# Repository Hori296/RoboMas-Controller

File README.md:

# RoboMaster Controller

STM32を用いて設計・開発した、RoboMaster M2006 / M3508用モータコントローラです。

本リポジトリでは、回路設計・基板設計・ファームウェアを公開しています。
ロボット開発や組込みシステムで再利用できることを目的として製作しました。

---

## 概要

本コントローラは、DJI RoboMasterシリーズのM2006・M3508モータをCAN通信で制御するためのモータコントローラです。

速度制御・位置制御の両方に対応しており、連続角度推定やソフトウェアによる原点リセットなど、ロボット開発で扱いやすい機能を実装しています。

---

## 主な機能

- M2006 / M3508 モータ対応
- CAN通信による制御
- 速度制御（PID）
- 位置制御（カスケードPID）
- エンコーダ多回転角度推定
- ソフトウェア原点リセット
- 通信タイムアウト保護（500 ms）
- デバッグ情報送信（速度・位置誤差）
- RGB LEDによる状態表示

---

## 設計方針・意図

本コントローラは、M2006・M3508を今後のロボット開発で繰り返し利用できることを目的として設計しています。  
機能追加を前提とするのではなく、速度制御・位置制御・多回転角度推定・通信タイムアウト保護など、実際のロボット運用に必要な機能を一つの基板にまとめています。  
私自身がM2006・M3508モータを複数所有しており、今後のロボット開発でも継続して使用する予定です。そのため、毎回制御プログラムを作り直すことなく、共通で利用できるモータコントローラとして設計しました。

---

## ハードウェア

### マイコン

- STM32F446RE

### 通信

- CAN1
    - 上位PC・マイコンとの通信
- CAN2
    - RoboMaster ESCとの通信

### 制御周期

- 制御周期：1 ms（タイマ割り込み）
- CAN受信：受信割り込み

---

## 通信仕様

### 制御コマンド
|ID|num|
|---|---|
|0x221|motor1|
|0x222|motor2|
|0x223|motor3|
|0x224|motor4|

|Byte|内容|
|---|---|
|0|モータ種類|
|1|制御モード|
|2-3|目標値(int16 /1000)|
|4|Enable|
|5|角度リセット|
|6-7|予約|

### モータ種類

|値|内容|
|---|---|
|1|M2006|
|2|M3508|

### 制御モード

|値|内容|
|---|---|
|1|速度制御|
|2|位置制御|

### デバッグ情報

|ID|0~1|2~3|4~5|6~7|
|---|---|---|---|---|
|0x220|motor1_diff|motor2_diff|motor3_diff|motor4_diff|

---

## 安全機能

500 ms以上制御コマンドを受信しなかった場合、

- モータ停止
- PIDリセット
- 出力0

を実行し、通信断による暴走を防止します。

---

## 写真

|基板|3D|
|---|---|
|||

---

## 動作

※gif画像のためにいろいろしたら，LEDの色おかしくなった( ˊᵕˋ ;)

---

## フォルダ構成

```
Firmware/
    inc
    src
    README

PCB/
    pcb
    sch
    step
    production (JLCPCB発注用)
    README
```

---

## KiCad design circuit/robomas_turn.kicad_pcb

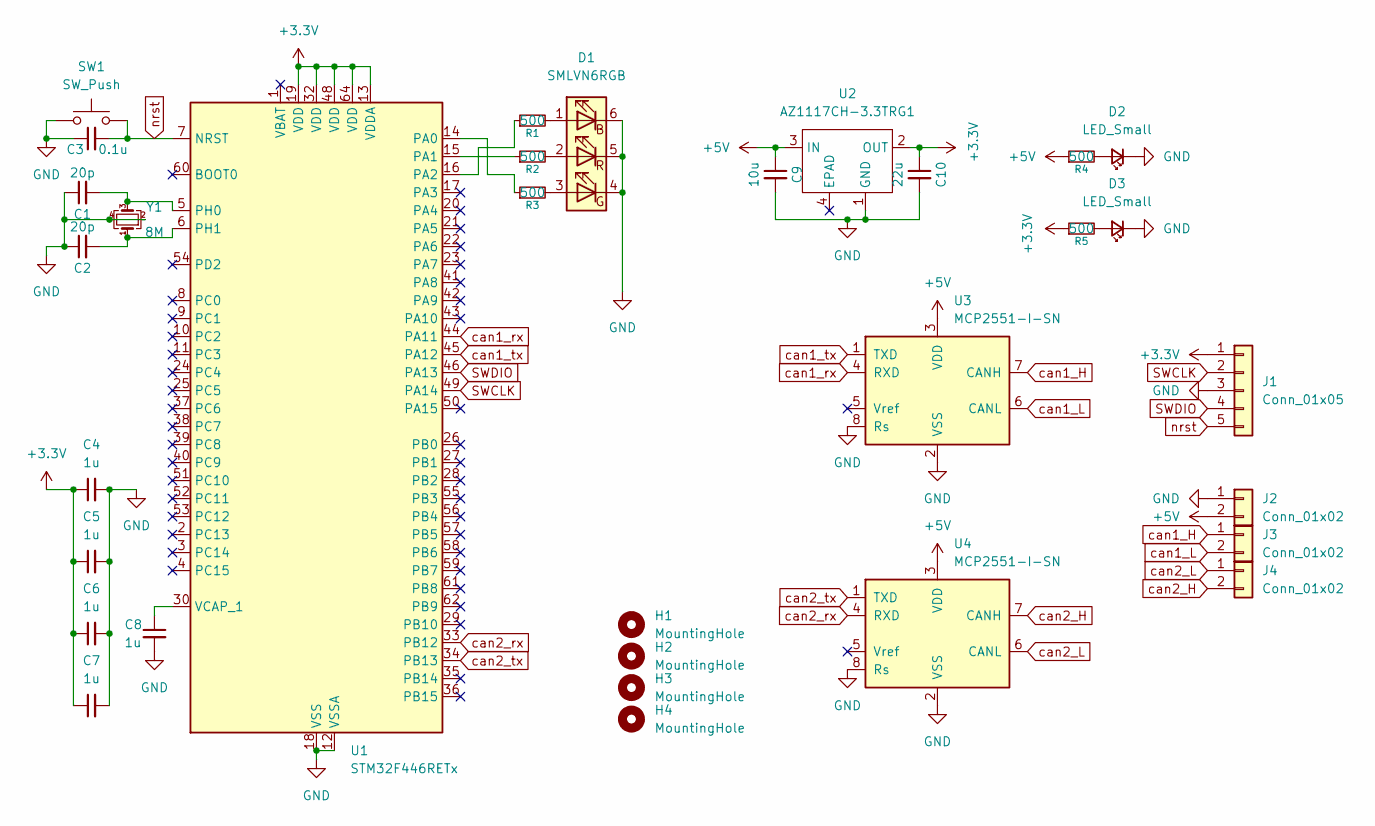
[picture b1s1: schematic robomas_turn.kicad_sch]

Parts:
C1, C2: 20p; C_0603_1608Metric
C3: 0.1u; C_0603_1608Metric
C4, C5, C6, C7, C8: 1u; C_0603_1608Metric
C9: 10u; C_0603_1608Metric
C10: 22u; C_0603_1608Metric
D1: SMLVN6RGB; LED_ROHM_SMLVN6
D2, D3: LED_Small; LED_0603_1608Metric
H1, H2, H3, H4: MountingHole; MountingHole_3.2mm_M3_Pad_Via
J1: Conn_01x05; PinSocket_1x05_P2.54mm_Vertical
J2, J3, J4: Conn_01x02; JST_XA_S02B-XASK-1_1x02_P2.50mm_Horizontal
R1, R2, R3, R4, R5: 500; R_0603_1608Metric
SW1: SW_Push; SW_Push_1P1T_NO_CK_KMR2
U1: STM32F446RETx; LQFP-64_10x10mm_P0.5mm
U2: AZ1117CH-3.3TRG1; SOT-223
U3, U4: MCP2551-I-SN; SOIC-8_3.9x4.9mm_P1.27mm
Y1: 8M; Crystal_SMD_5032-4Pin_5.0x3.2mm

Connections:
+3.3V: C4.1, C5.1, C6.1, C7.1, C10.1, J1.1, R5.1, U1.13 (VDDA), U1.19 (VDD), U1.32 (VDD), U1.48 (VDD), U1.64 (VDD), U2.2 (OUT)
+5V: C9.1, J2.2, R4.1, U2.3 (IN), U3.3 (VDD), U4.3 (VDD)
GND: C1.1, C2.1, C3.1, C4.2, C5.2, C6.2, C7.2, C8.2, C9.2, C10.2, D1.4 (GK), D1.5 (RK), D1.6 (BK), D2.1 (K), D3.1 (K), J1.3, J2.1, SW1.1, U1.12 (VSSA), U1.18 (VSS), U1.31 (VSS), U1.47 (VSS), U1.63 (VSS), U2.1 (GND), U3.2 (VSS), U3.8 (Rs), U4.2 (VSS), U4.8 (Rs), Y1.2, Y1.4
unnamed: D1.1 (BA), R1.2
unnamed: D1.3 (GA), R3.2
unnamed: D1.2 (RA), R2.2
unnamed: D2.2 (A), R4.2
unnamed: D3.2 (A), R5.2
unnamed: R3.1, U1.14 (PA0)
unnamed: R2.1, U1.15 (PA1)
unnamed: R1.1, U1.16 (PA2)
unnamed: C1.2, U1.5 (PH0), Y1.3
unnamed: C2.2, U1.6 (PH1), Y1.1
unnamed: C8.1, U1.30 (VCAP_1)
SWCLK: J1.2, U1.49 (PA14)
SWDIO: J1.4, U1.46 (PA13)
can1_H: J3.1, U3.7 (CANH)
can1_L: J3.2, U3.6 (CANL)
can1_rx: U1.44 (PA11), U3.4 (RXD)
can1_tx: U1.45 (PA12), U3.1 (TXD)
can2_H: J4.2, U4.7 (CANH)
can2_L: J4.1, U4.6 (CANL)
can2_rx: U1.33 (PB12), U4.4 (RXD)
can2_tx: U1.34 (PB13), U4.1 (TXD)
nrst: C3.2, J1.5, SW1.2, U1.7 (NRST)

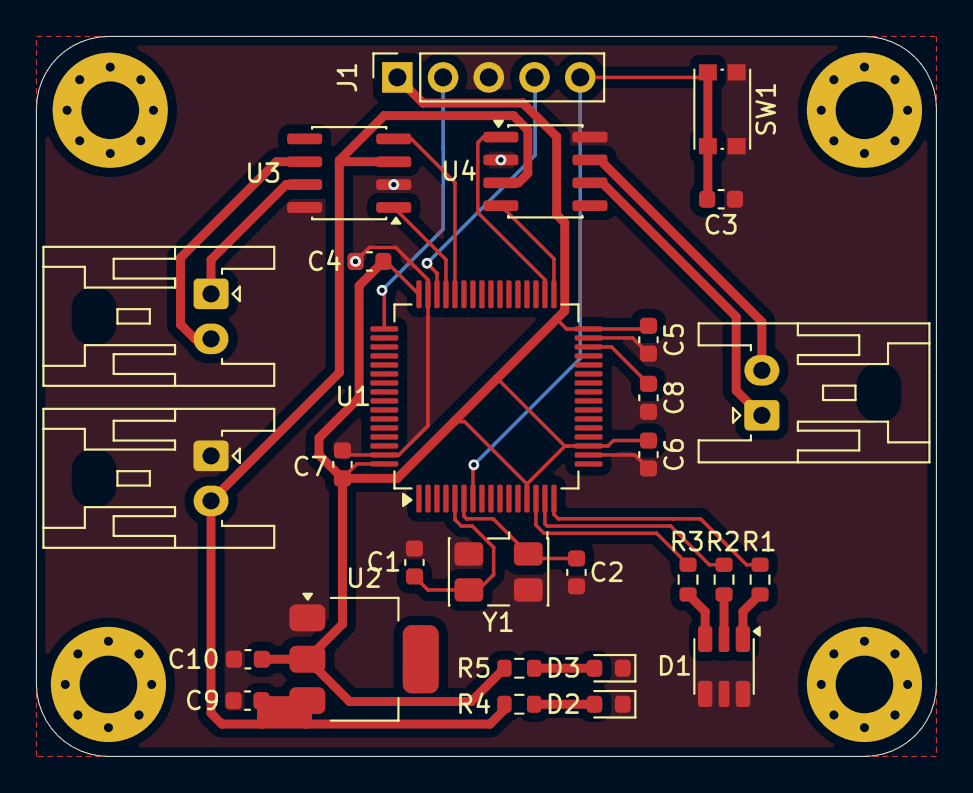
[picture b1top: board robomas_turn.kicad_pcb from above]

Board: 2 copper layers, 50.0 x 40.0 mm, 32 parts (0 on the bottom side), 25 nets.

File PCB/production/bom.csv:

Designator,Footprint,Quantity,Value,LCSC Part #
"C1, C2",0603,2,20p,
C10,0603,1,22u,
C3,0603,1,0.1u,
"C4, C5, C6, C7, C8",0603,5,1u,
C9,0603,1,10u,
D1,LED_ROHM_SMLVN6,1,SMLVN6RGB,
"D2, D3",0603,2,LED_Small,
"H1, H2, H3, H4",MountingHole_3.2mm_M3_Pad_Via,4,MountingHole,
J1,PinSocket_1x05_P2.54mm_Vertical,1,Conn_01x05,
"J2, J3, J4",JST_XA_S02B-XASK-1_1x02_P2.50mm_Horizontal,3,Conn_01x02,
"R1, R2, R3, R4, R5",0603,5,500,
SW1,SW_Push_1P1T_NO_CK_KMR2,1,SW_Push,
U1,LQFP-64_10x10mm_P0.5mm,1,STM32F446RETx,
U2,SOT-223,1,AZ1117CH-3.3TRG1,
"U3, U4",SOIC-8_3.9x4.9mm_P1.27mm,2,MCP2551-I-SN,
Y1,Crystal_SMD_5032-4Pin_5.0x3.2mm,1,8M,
